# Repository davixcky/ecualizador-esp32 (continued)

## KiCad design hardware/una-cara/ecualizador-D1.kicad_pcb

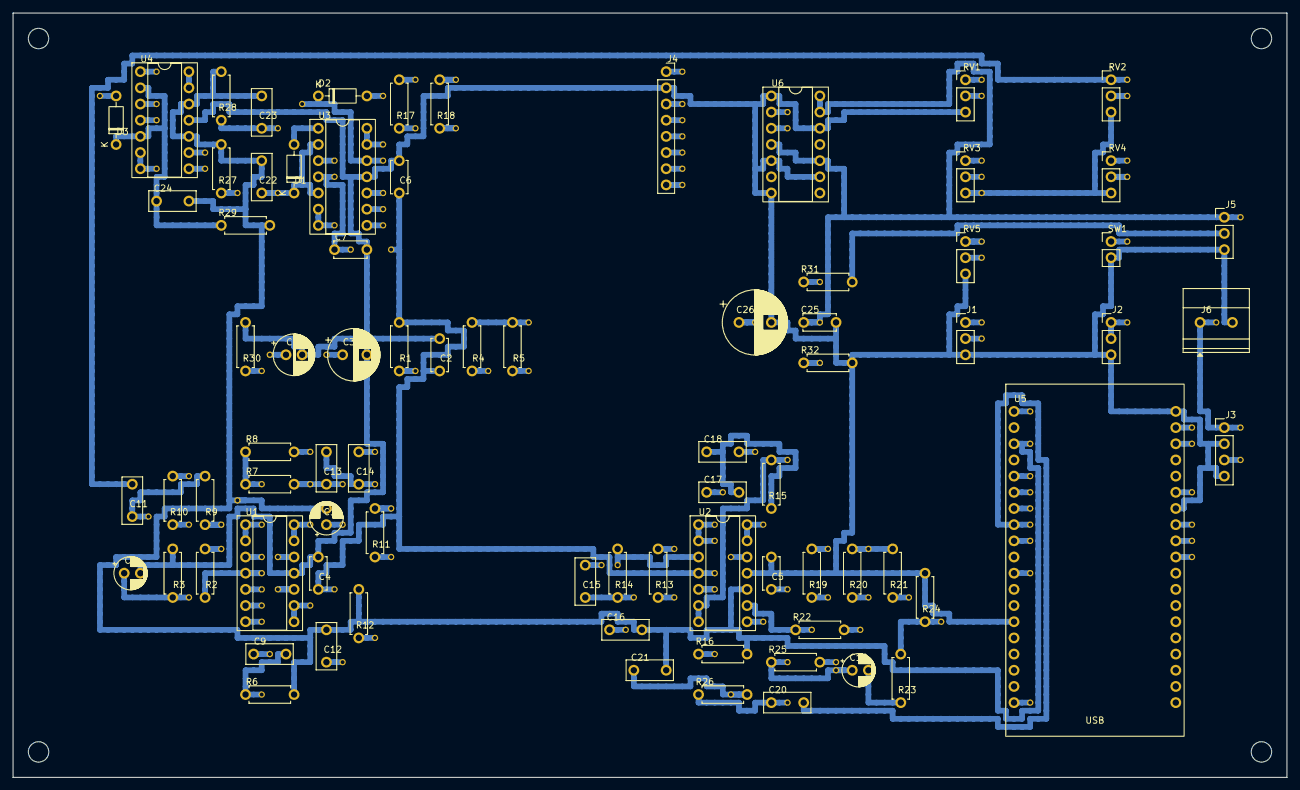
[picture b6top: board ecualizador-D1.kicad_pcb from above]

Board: 2 copper layers, 200.0 x 120.0 mm, 163 parts (0 on the bottom side), 59 nets.

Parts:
C1: 100u 10V; UnaCara_C1
C2: 100n; UnaCara_C2
C3: 470u 10V; UnaCara_C3
C4: 100n; UnaCara_C4
C5: 100n; UnaCara_C5
C6: 100n; UnaCara_C6
C7: 100n; UnaCara_C7
C8: 10u 16V; UnaCara_C8
C9: 1u film; UnaCara_C9
C10: 10u 16V; UnaCara_C10
C11: 100n film; UnaCara_C11
C12: 47n film; UnaCara_C12
C13: 10n film; UnaCara_C13
C14: 10n film; UnaCara_C14
C15: 10n film; UnaCara_C15
C16: 4n7 film; UnaCara_C16
C17: 10n film; UnaCara_C17
C18: 10n film; UnaCara_C18
C19: 10u 16V; UnaCara_C19
C20: 4n7 film; UnaCara_C20
C21: 2n2 film; UnaCara_C21
C22: 100n film; UnaCara_C22
C23: 100n film; UnaCara_C23
C24: 100n film; UnaCara_C24
C25: 100n; UnaCara_C25
C26: 1000u 10V; UnaCara_C26
D1: 1N4148; UnaCara_D1
D2: 1N4148; UnaCara_D2
D3: 1N4148; UnaCara_D3
H1, H2, H3, H4: MountingHole_3.2mm_M3
J1: Entrada de línea 3,5 mm; UnaCara_J1
J2: Salida de línea 3,5 mm; UnaCara_J2
J3: PAM8403; UnaCara_J3
J4: Waveshare 1.9 ST7789V2; UnaCara_J4
J5: NeoPixel 5V DIN GND; UnaCara_J5
J6: Entrada 5V 3A; UnaCara_J6
R1: 10; UnaCara_R1
R2: 10k 1%; UnaCara_R2
R3: 10k 1%; UnaCara_R3
R4: 10k; UnaCara_R4
R5: 10k; UnaCara_R5
R6: 100k; UnaCara_R6
R7: 22k 1%; UnaCara_R7
R8: 10k 1%; UnaCara_R8
R9: 10k 1%; UnaCara_R9
R10: 10k 1%; UnaCara_R10
R11: 27k 1%; UnaCara_R11
R12: 56k 1%; UnaCara_R12
R13: 10k 1%; UnaCara_R13
R14: 10k 1%; UnaCara_R14
R15: 2k7 1%; UnaCara_R15
R16: 5k6 1%; UnaCara_R16
R17: 47k 1%; UnaCara_R17
R18: 47k 1%; UnaCara_R18
R19: 47k 1%; UnaCara_R19
R20: 47k 1%; UnaCara_R20
R21: 47k 1%; UnaCara_R21
R22: 100k 1%; UnaCara_R22
R23: 100; UnaCara_R23
R24: 47k; UnaCara_R24
R25: 10k 1%; UnaCara_R25
R26: 10k 1%; UnaCara_R26
R27: 220k; UnaCara_R27
R28: 220k; UnaCara_R28
R29: 220k; UnaCara_R29
R30: 10k; UnaCara_R30
R31: 330; UnaCara_R31
R32: 10k; UnaCara_R32
RV1: 10k log; UnaCara_RV1
RV2: 10k lin; UnaCara_RV2
RV3: 10k lin; UnaCara_RV3
RV4: 10k lin; UnaCara_RV4
RV5: 10k log; UnaCara_RV5
SW1: Pulsador; UnaCara_SW1
U1: MCP6004; UnaCara_U1
U2: MCP6004; UnaCara_U2
U3: MCP6004; UnaCara_U3
U4: MCP6004; UnaCara_U4
U5: ESP32-DevKitC V4; UnaCara_U5
U6: 74AHCT125; UnaCara_U6
W1, W2: Cable aislado /VREF
W3, W4, W5, W6, W7: Cable aislado +3.3VA
W8, W9, W10, W11: Cable aislado +5V
W12, W13: Cable aislado /LINEA
W14, W15, W16: Cable aislado /PRE
W17: Cable aislado Net-(D1-K)
W18, W19: Cable aislado Net-(D2-K)
W20, W21: Cable aislado Net-(U2C--)
W22: Cable aislado /ADC_FFT
W23: Cable aislado /AGUDOS
W24, W25: Cable aislado /EQ_OUT
W26: Cable aislado /GRAVES
W27, W28: Cable aislado /MEDIOS
W29, W30: Cable aislado /MED_HP
W31, W32: Cable aislado Net-(U1A-+)
W33, W34: Cable aislado +3V3
W35: Cable aislado /ADC_A
W36: Cable aislado /ADC_G
W37: Cable aislado /ADC_M
W38, W39: Cable aislado /A_W
W40, W41: Cable aislado /G_W
W42, W43: Cable aislado /LED_DATA
W44, W45: Cable aislado /M_INV
W46, W47: Cable aislado /M_W
W48, W49: Cable aislado /TFT_BL
W50: Cable aislado Net-(C11-Pad1)
W51: Cable aislado Net-(C13-Pad2)
W52: Cable aislado Net-(C15-Pad1)
W53: Cable aislado Net-(C20-Pad1)
W54: Cable aislado Net-(R4-Pad2)
W55: Cable aislado Net-(U1B-+)
W56: Cable aislado Net-(U1B--)
W57, W58: Cable aislado Net-(U1C-+)
W59, W60: Cable aislado Net-(U1D-+)
W61: Cable aislado Net-(U2A-+)
W62, W63: Cable aislado Net-(U2B-+)
W64: Cable aislado Net-(U2D-+)
W65, W66: Cable aislado Net-(U4C--)
W67: Cable aislado /AMP_IN
W68: Cable aislado /BTN
W69: Cable aislado /IN_L
W70: Cable aislado /IN_R
W71: Cable aislado /LED_5V
W72: Cable aislado /TFT_CS
W73: Cable aislado /TFT_DC
W74: Cable aislado /TFT_MOSI
W75: Cable aislado /TFT_RST
W76: Cable aislado /TFT_SCK
W77: Cable aislado Net-(C10-Pad1)
W78: Cable aislado Net-(C9-Pad1)
W79: Cable aislado Net-(D2-A)
W80: Cable aislado Net-(D3-A)

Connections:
+3.3VA: C1.1, C2.1, C4.1, C5.1, C6.1, C7.1, R1.2, R2.1, U1.4, U2.4, U3.4, U4.4, W3.1, W3.2, W4.1, W4.2, W5.1, W5.2, W6.1, W6.2, W7.1, W7.2
+3V3: J4.1, R1.1, U5.1, W33.1, W33.2, W34.1, W34.2
+5V: C3.1, C25.1, C26.1, J3.1, J5.1, J6.1, U5.19, U6.4, U6.10, U6.13, U6.14, W8.1, W8.2, W9.1, W9.2, W10.1, W10.2, W11.1, W11.2
/ADC_A: U4.6, U4.7, U5.7, W35.1, W35.2
/ADC_FFT: C20.2, U2.13, U2.14, U5.8, W22.1, W22.2
/ADC_G: U3.6, U3.7, U5.5, W36.1, W36.2
/ADC_M: U3.13, U3.14, U5.6, W37.1, W37.2
/AGUDOS: R15.2, RV4.1, U2.6, U2.7, W23.1, W23.2
/AMP_IN: J3.3, RV5.2, W67.1, W67.2
/A_W: R21.1, RV4.2, U4.3, W38.1, W38.2, W39.1, W39.2
/BTN: SW1.1, U5.11, W68.1, W68.2
/EQ_OUT: C19.1, R22.2, R25.1, U2.8, W24.1, W24.2, W25.1, W25.2
/GRAVES: C11.2, RV2.1, U1.8, U1.9, W26.1, W26.2
/G_W: R19.1, RV2.2, U3.3, W40.1, W40.2, W41.1, W41.2
/IN_L: J1.T, R4.1, W69.1, W69.2
/IN_R: J1.R, R5.1, W70.1, W70.2
/LED_5V: R31.1, U6.3, W71.1, W71.2
/LED_DATA: R32.1, U5.9, U6.2, W42.1, W42.2, W43.1, W43.2
/LED_DIN: J5.2, R31.2
/LINEA: J2.R, J2.T, R23.2, R24.1, RV5.1, W12.1, W12.2, W13.1, W13.2
/MEDIOS: C15.2, RV3.1, U2.1, U2.2, W27.1, W27.2, W28.1, W28.2
/MED_HP: R11.2, R13.1, U1.13, U1.14, W29.1, W29.2, W30.1, W30.2
/M_INV: R18.2, R20.1, U4.8, W44.1, W44.2, W45.1, W45.2
/M_W: R17.1, RV3.2, U3.10, W46.1, W46.2, W47.1, W47.2
/PRE: C13.1, C17.1, R7.2, R9.1, U1.7, W14.1, W14.2, W15.1, W15.2, W16.1, W16.2
/TFT_BL: J4.8, R30.1, U5.27, W48.1, W48.2, W49.1, W49.2
/TFT_CS: J4.5, U5.29, W72.1, W72.2
/TFT_DC: J4.6, U5.25, W73.1, W73.2
/TFT_MOSI: J4.3, U5.21, W74.1, W74.2
/TFT_RST: J4.7, U5.22, W75.1, W75.2
/TFT_SCK: J4.4, U5.28, W76.1, W76.2
/VREF: C10.2, C12.2, C16.2, C21.2, C22.2, C23.2, C24.2, R6.2, R12.2, R16.2, R27.2, R28.2, R29.2, RV2.3, RV3.3, RV4.3, U1.1, U1.2, U2.10, U4.10, U4.12, U5.3, W1.1, W1.2, W2.1, W2.2
GND: C1.2, C2.2, C3.2, C4.2, C5.2, C6.2, C7.2, C8.2, C25.2, C26.2, J1.S, J2.S, J3.2, J3.4, J4.2, J5.3, J6.2, R3.2, R24.2, R30.2, R32.2, RV1.3, RV5.3, SW1.2, U1.11, U2.11, U3.11, U4.11, U5.14, U5.20, U5.26, U6.1, U6.5, U6.7, U6.9, U6.12
unnamed: C9.1, RV1.2, W78.1, W78.2
unnamed: C10.1, R8.2, W77.1, W77.2
unnamed: C11.1, R9.2, R10.1, W50.1, W50.2
unnamed: C13.2, C14.1, R11.1, W51.1, W51.2
unnamed: C15.1, R13.2, R14.1, W52.1, W52.2
unnamed: C17.2, C18.1, R15.1
unnamed: C19.2, R23.1
unnamed: C20.1, R25.2, R26.1, W53.1, W53.2
unnamed: D1.2, U3.1
unnamed: C22.1, D1.1, R27.1, U3.2, U3.5, W17.1, W17.2
unnamed: D2.2, U3.8, W79.1, W79.2
unnamed: C23.1, D2.1, R28.1, U3.9, U3.12, W18.1, W18.2, W19.1, W19.2
unnamed: D3.2, U4.1, W80.1, W80.2
unnamed: C24.1, D3.1, R29.1, U4.2, U4.5
unnamed: R4.2, R5.2, RV1.1, W54.1, W54.2
unnamed: C8.1, R2.2, R3.1, U1.3, W31.1, W31.2, W32.1, W32.2
unnamed: C9.2, R6.1, U1.5, W55.1, W55.2
unnamed: R7.1, R8.1, U1.6, W56.1, W56.2
unnamed: C12.1, R10.2, U1.10, W57.1, W57.2, W58.1, W58.2
unnamed: C14.2, R12.1, U1.12, W59.1, W59.2, W60.1, W60.2
unnamed: C16.1, R14.2, U2.3, W61.1, W61.2
unnamed: C18.2, R16.1, U2.5, W62.1, W62.2, W63.1, W63.2
unnamed: R19.2, R20.2, R21.2, R22.1, U2.9, W20.1, W20.2, W21.1, W21.2
unnamed: C21.1, R26.2, U2.12, W64.1, W64.2
unnamed: R17.2, R18.1, U4.9, W65.1, W65.2, W66.1, W66.2
unnamed: U4.13, U4.14

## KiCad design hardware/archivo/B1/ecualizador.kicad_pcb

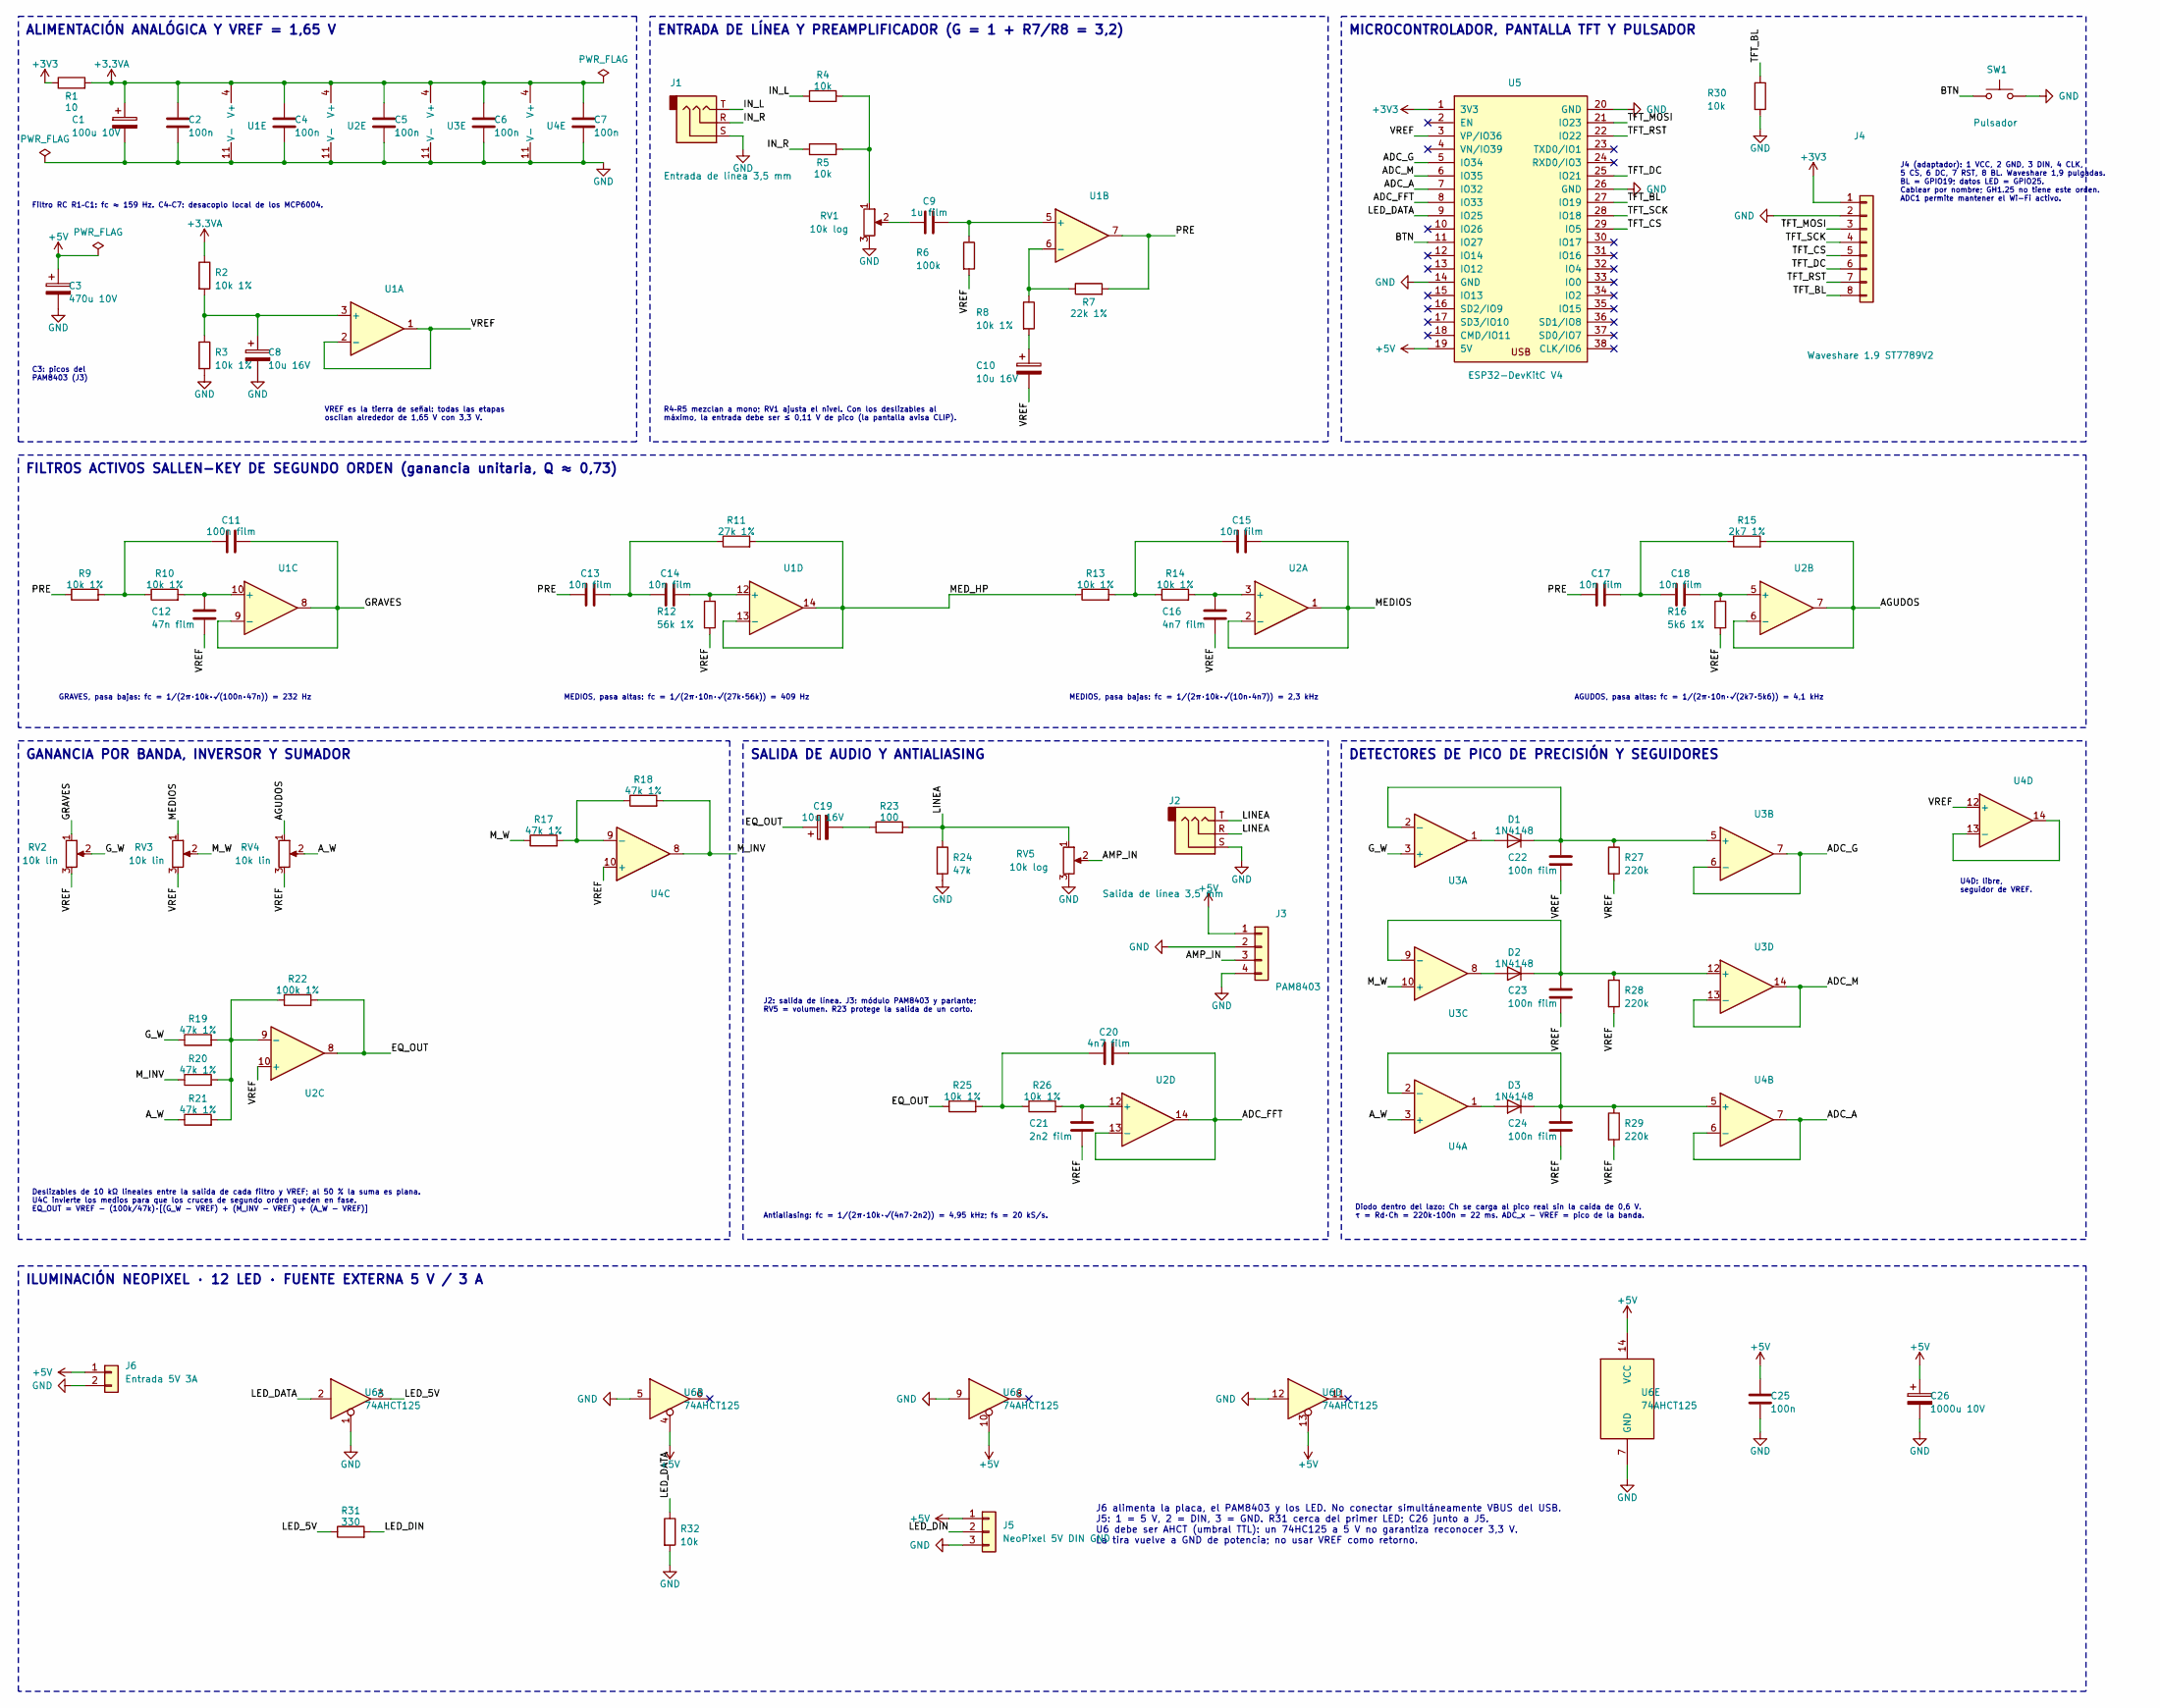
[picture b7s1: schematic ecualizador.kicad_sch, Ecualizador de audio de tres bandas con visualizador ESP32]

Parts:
C1: 100u 10V; UnaCara_C1
C2: 100n; UnaCara_C2
C3: 470u 10V; UnaCara_C3
C4: 100n; UnaCara_C4
C5: 100n; UnaCara_C5
C6: 100n; UnaCara_C6
C7: 100n; UnaCara_C7
C8: 10u 16V; UnaCara_C8
C9: 1u film; UnaCara_C9
C10: 10u 16V; UnaCara_C10
C11: 100n film; UnaCara_C11
C12: 47n film; UnaCara_C12
C13: 10n film; UnaCara_C13
C14: 10n film; UnaCara_C14
C15: 10n film; UnaCara_C15
C16: 4n7 film; UnaCara_C16
C17: 10n film; UnaCara_C17
C18: 10n film; UnaCara_C18
C19: 10u 16V; UnaCara_C19
C20: 4n7 film; UnaCara_C20
C21: 2n2 film; UnaCara_C21
C22: 100n film; UnaCara_C22
C23: 100n film; UnaCara_C23
C24: 100n film; UnaCara_C24
C25: 100n; UnaCara_C25
C26: 1000u 10V; UnaCara_C26
D1: 1N4148; UnaCara_D1
D2: 1N4148; UnaCara_D2
D3: 1N4148; UnaCara_D3
J1: Entrada de línea 3,5 mm; UnaCara_J1
J2: Salida de línea 3,5 mm; UnaCara_J2
J3: PAM8403; UnaCara_J3
J4: Waveshare 1.9 ST7789V2; UnaCara_J4
J5: NeoPixel 5V DIN GND; UnaCara_J5
J6: Entrada 5V 3A; UnaCara_J6
R1: 10; UnaCara_R1
R2: 10k 1%; UnaCara_R2
R3: 10k 1%; UnaCara_R3
R4: 10k; UnaCara_R4
R5: 10k; UnaCara_R5
R6: 100k; UnaCara_R6
R7: 22k 1%; UnaCara_R7
R8: 10k 1%; UnaCara_R8
R9: 10k 1%; UnaCara_R9
R10: 10k 1%; UnaCara_R10
R11: 27k 1%; UnaCara_R11
R12: 56k 1%; UnaCara_R12
R13: 10k 1%; UnaCara_R13
R14: 10k 1%; UnaCara_R14
R15: 2k7 1%; UnaCara_R15
R16: 5k6 1%; UnaCara_R16
R17: 47k 1%; UnaCara_R17
R18: 47k 1%; UnaCara_R18
R19: 47k 1%; UnaCara_R19
R20: 47k 1%; UnaCara_R20
R21: 47k 1%; UnaCara_R21
R22: 100k 1%; UnaCara_R22
R23: 100; UnaCara_R23
R24: 47k; UnaCara_R24
R25: 10k 1%; UnaCara_R25
R26: 10k 1%; UnaCara_R26
R27: 220k; UnaCara_R27
R28: 220k; UnaCara_R28
R29: 220k; UnaCara_R29
R30: 10k; UnaCara_R30
R31: 330; UnaCara_R31
R32: 10k; UnaCara_R32
RV1: 10k log; UnaCara_RV1
RV2: 10k lin; UnaCara_RV2
RV3: 10k lin; UnaCara_RV3
RV4: 10k lin; UnaCara_RV4
RV5: 10k log; UnaCara_RV5
SW1: Pulsador; UnaCara_SW1
U1: MCP6004; UnaCara_U1
U2: MCP6004; UnaCara_U2
U3: MCP6004; UnaCara_U3
U4: MCP6004; UnaCara_U4
U5: ESP32-DevKitC V4; UnaCara_U5
U6: 74AHCT125; UnaCara_U6

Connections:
+3.3VA: C1.1, C2.1, C4.1, C5.1, C6.1, C7.1, R1.2, R2.1, U1.4 (V+), U2.4 (V+), U3.4 (V+), U4.4 (V+)
+3V3: J4.1, R1.1, U5.1 (3V3)
+5V: C3.1, C25.1, C26.1, J3.1, J5.1, J6.1, U5.19 (5V), U6.4, U6.10, U6.13, U6.14 (VCC)
/ADC_A: U4.6 (-), U4.7, U5.7 (IO32)
/ADC_FFT: C20.2, U2.13 (-), U2.14, U5.8 (IO33)
/ADC_G: U3.6 (-), U3.7, U5.5 (IO34)
/ADC_M: U3.13 (-), U3.14, U5.6 (IO35)
/AGUDOS: R15.2, RV4.1, U2.6 (-), U2.7
/AMP_IN: J3.3, RV5.2
/A_W: R21.1, RV4.2, U4.3 (+)
/BTN: SW1.1, U5.11 (IO27)
/EQ_OUT: C19.1, R22.2, R25.1, U2.8
/GRAVES: C11.2, RV2.1, U1.8, U1.9 (-)
/G_W: R19.1, RV2.2, U3.3 (+)
/IN_L: J1.T, R4.1
/IN_R: J1.R, R5.1
/LED_5V: R31.1, U6.3
/LED_DATA: R32.1, U5.9 (IO25), U6.2
/LED_DIN: J5.2, R31.2
/LINEA: J2.R, J2.T, R23.2, R24.1, RV5.1
/MEDIOS: C15.2, RV3.1, U2.1, U2.2 (-)
/MED_HP: R11.2, R13.1, U1.13 (-), U1.14
/M_INV: R18.2, R20.1, U4.8
/M_W: R17.1, RV3.2, U3.10 (+)
/PRE: C13.1, C17.1, R7.2, R9.1, U1.7
/TFT_BL: J4.8, R30.1, U5.27 (IO19)
/TFT_CS: J4.5, U5.29 (IO5)
/TFT_DC: J4.6, U5.25 (IO21)
/TFT_MOSI: J4.3, U5.21 (IO23)
/TFT_RST: J4.7, U5.22 (IO22)
/TFT_SCK: J4.4, U5.28 (IO18)
/VREF: C10.2, C12.2, C16.2, C21.2, C22.2, C23.2, C24.2, R6.2, R12.2, R16.2, R27.2, R28.2, R29.2, RV2.3, RV3.3, RV4.3, U1.1, U1.2 (-), U2.10 (+), U4.10 (+), U4.12 (+), U5.3 (VP/IO36)
GND: C1.2, C2.2, C3.2, C4.2, C5.2, C6.2, C7.2, C8.2, C25.2, C26.2, J1.S, J2.S, J3.2, J3.4, J4.2, J5.3, J6.2, R3.2, R24.2, R30.2, R32.2, RV1.3, RV5.3, SW1.2, U1.11 (V-), U2.11 (V-), U3.11 (V-), U4.11 (V-), U5.14 (GND), U5.20 (GND), U5.26 (GND), U6.1, U6.5, U6.7 (GND), U6.9, U6.12
unnamed: C9.1, RV1.2
unnamed: C10.1, R8.2
unnamed: C11.1, R9.2, R10.1
unnamed: C13.2, C14.1, R11.1
unnamed: C15.1, R13.2, R14.1
unnamed: C17.2, C18.1, R15.1
unnamed: C19.2, R23.1
unnamed: C20.1, R25.2, R26.1
unnamed: D1.2 (A), U3.1
unnamed: C22.1, D1.1 (K), R27.1, U3.2 (-), U3.5 (+)
unnamed: D2.2 (A), U3.8
unnamed: C23.1, D2.1 (K), R28.1, U3.9 (-), U3.12 (+)
unnamed: D3.2 (A), U4.1
unnamed: C24.1, D3.1 (K), R29.1, U4.2 (-), U4.5 (+)
unnamed: R4.2, R5.2, RV1.1
unnamed: C8.1, R2.2, R3.1, U1.3 (+)
unnamed: C9.2, R6.1, U1.5 (+)
unnamed: R7.1, R8.1, U1.6 (-)
unnamed: C12.1, R10.2, U1.10 (+)
unnamed: C14.2, R12.1, U1.12 (+)
unnamed: C16.1, R14.2, U2.3 (+)
unnamed: C18.2, R16.1, U2.5 (+)
unnamed: R19.2, R20.2, R21.2, R22.1, U2.9 (-)
unnamed: C21.1, R26.2, U2.12 (+)
unnamed: R17.2, R18.1, U4.9 (-)
unnamed: U4.13 (-), U4.14

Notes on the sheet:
ALIMENTACIÓN ANALÓGICA Y VREF = 1,65 V
Filtro RC R1–C1: fc ≈ 159 Hz. C4–C7: desacoplo local de los MCP6004.
C3: picos del PAM8403 (J3)
VREF es la tierra de señal: todas las etapas oscilan alrededor de 1,65 V con 3,3 V.
ENTRADA DE LÍNEA Y PREAMPLIFICADOR (G = 1 + R7/R8 = 3,2)
R4–R5 mezclan a mono; RV1 ajusta el nivel. Con los deslizables al máximo, la entrada debe ser ≤ 0,11 V de pico (la pantalla avisa CLIP).
MICROCONTROLADOR, PANTALLA TFT Y PULSADOR
J4 (adaptador): 1 VCC, 2 GND, 3 DIN, 4 CLK, 5 CS, 6 DC, 7 RST, 8 BL. Waveshare 1,9 pulgadas. BL = GPIO19; datos LED = GPIO25. Cablear por nombre; GH1.25 no tiene este orden. ADC1 permite mantener el Wi-Fi activo.
FILTROS ACTIVOS SALLEN-KEY DE SEGUNDO ORDEN (ganancia unitaria, Q ≈ 0,73)
GRAVES, pasa bajas: fc = 1/(2π·10k·√(100n·47n)) = 232 Hz
MEDIOS, pasa altas: fc = 1/(2π·10n·√(27k·56k)) = 409 Hz
MEDIOS, pasa bajas: fc = 1/(2π·10k·√(10n·4n7)) = 2,3 kHz
AGUDOS, pasa altas: fc = 1/(2π·10n·√(2k7·5k6)) = 4,1 kHz
GANANCIA POR BANDA, INVERSOR Y SUMADOR
Deslizables de 10 kΩ lineales entre la salida de cada filtro y VREF; al 50 % la suma es plana. U4C invierte los medios para que los cruces de segundo orden queden en fase. EQ_OUT = VREF − (100k/47k)·[(G_W − VREF) + (M_INV − VREF) + (A_W − VREF)]
SALIDA DE AUDIO Y ANTIALIASING
J2: salida de línea. J3: módulo PAM8403 y parlante; RV5 = volumen. R23 protege la salida de un corto.
Antialiasing: fc = 1/(2π·10k·√(4n7·2n2)) = 4,95 kHz; fs = 20 kS/s.
DETECTORES DE PICO DE PRECISIÓN Y SEGUIDORES
U4D: libre, seguidor de VREF.
Diodo dentro del lazo: Ch se carga al pico real sin la caída de 0,6 V. τ = Rd·Ch = 220k·100n = 22 ms. ADC_x − VREF = pico de la banda.
ILUMINACIÓN NEOPIXEL · 12 LED · FUENTE EXTERNA 5 V / 3 A
J6 alimenta la placa, el PAM8403 y los LED. No conectar simultáneamente VBUS del USB. J5: 1 = 5 V, 2 = DIN, 3 = GND. R31 cerca del primer LED; C26 junto a J5. U6 debe ser AHCT (umbral TTL): un 74HC125 a 5 V no garantiza reconocer 3,3 V. La tira vuelve a GND de potencia; no usar VREF como retorno.

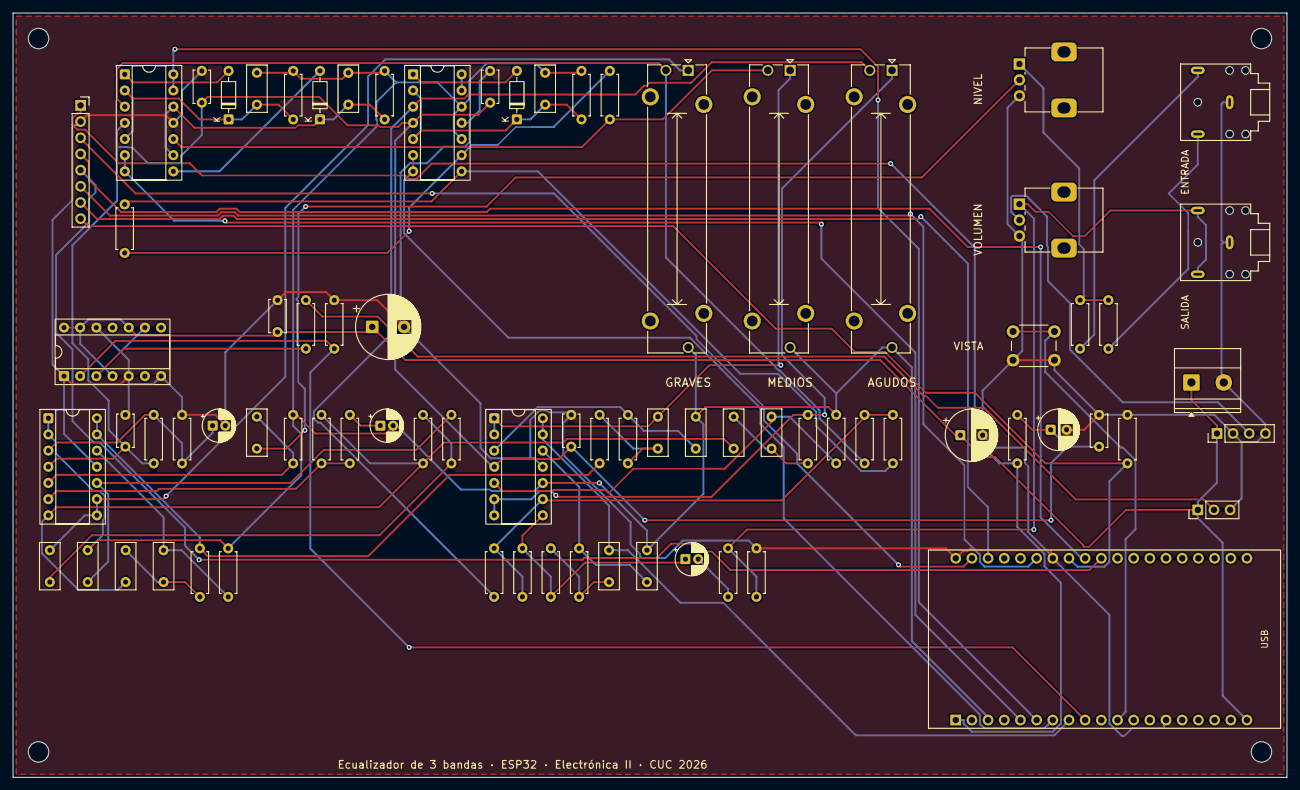
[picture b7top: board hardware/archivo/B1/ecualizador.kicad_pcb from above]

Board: 2 copper layers, 200.0 x 120.0 mm, 83 parts (0 on the bottom side), 59 nets.

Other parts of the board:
H1, H2, H3, H4: MountingHole_3.2mm_M3

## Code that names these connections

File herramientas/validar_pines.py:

#!/usr/bin/env python3
"""Cruza los GPIO del firmware con las señales del esquema, sin compilar ni alimentar la placa."""
from pathlib import Path
import re
import circuito
root=Path(__file__).resolve().parents[1]
config=(root/'firmware/include/config.h').read_text()
defines={k:int(v) for k,v in re.findall(r'^#define\s+(\w+)\s+(-?\d+)',config,re.M)}
mapping={'PIN_VREF':'VREF','PIN_GRAVES':'ADC_G','PIN_MEDIOS':'ADC_M','PIN_AGUDOS':'ADC_A','PIN_FFT':'ADC_FFT','PIN_BOTON':'BTN','PIN_NEOPIXEL':'LED_DATA',**{x:x for x in ['TFT_CS','TFT_DC','TFT_RST','TFT_MOSI','TFT_SCK','TFT_BL']}}
pins=[]
for define,net in mapping.items():
    gpio=defines[define]
    label='VP/IO36' if gpio==36 else f'IO{gpio}'
    assert circuito.ESP_REDES[label]==net,(define,net)
    pins.append(gpio)
assert len(pins)==len(set(pins)), 'GPIO compartido'
assert defines['TFT_MISO']==-1
assert circuito.pieza('U6')['pines']=={'1':'GND','2':'LED_DATA','3':'LED_5V','4':'+5V','5':'GND','6':None,'7':'GND','8':None,'9':'GND','10':'+5V','11':None,'12':'GND','13':'+5V','14':'+5V'}
print(f'{len(pins)} GPIO coinciden; ninguno compartido; MISO desactivado; pinout AHCT125 comprobado.')

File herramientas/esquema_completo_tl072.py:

from pathlib import Path
import matplotlib; matplotlib.use('Agg')
import matplotlib.pyplot as plt
from matplotlib.patches import Polygon,Rectangle,Circle
import csv,json
root=Path(__file__).resolve().parents[1];out=root/'docs/prototipo-tl072'
fig,ax=plt.subplots(figsize=(23.4,16.5)); ax.set(xlim=(0,2600),ylim=(1760,0));ax.axis('off');fig.subplots_adjust(0,0,1,1)
wire='#166447';ink='#122b38';red='#a3161a'; drawn={}
def line(*pts,color=wire,lw=1.15):ax.plot(*zip(*pts),color=color,lw=lw)
def text(x,y,s,size=9,color=ink,ha='center'):ax.text(x,y,s,fontsize=size,color=color,ha=ha,va='center',fontfamily='DejaVu Sans')
def dot(x,y):ax.add_patch(Circle((x,y),3.2,color=wire))
def ground(x,y):
 line((x,y),(x,y+15));line((x-13,y+15),(x+13,y+15));line((x-9,y+21),(x+9,y+21));line((x-4,y+27),(x+4,y+27))
def part(ref,val,x1,y1,x2,y2,kind='R',nets=None):
 if nets:drawn[ref]=(val,*nets)
 vertical=x1==x2;cx=(x1+x2)/2;cy=(y1+y2)/2
 if vertical:
  line((x1,y1),(cx,cy-22));line((cx,cy+22),(x2,y2))
  if kind=='R':ax.add_patch(Rectangle((cx-9,cy-22),18,44,fill=False,edgecolor=ink,lw=1.2))
  else:line((cx,cy-22),(cx,cy-5));line((cx,cy+5),(cx,cy+22));line((cx-17,cy-5),(cx+17,cy-5),color=ink);line((cx-17,cy+5),(cx+17,cy+5),color=ink)
  text(cx-20 if ref.startswith('RV') else cx+22,cy,ref+'\n'+val,8,ha='right' if ref.startswith('RV') else 'left')
 else:
  line((x1,y1),(cx-22,cy));line((cx+22,cy),(x2,y2))
  if kind=='R':ax.add_patch(Rectangle((cx-22,cy-9),44,18,fill=False,edgecolor=ink,lw=1.2))
  else:line((cx-22,cy),(cx-5,cy));line((cx+5,cy),(cx+22,cy));line((cx-5,cy-17),(cx-5,cy+17),color=ink);line((cx+5,cy-17),(cx+5,cy+17),color=ink)
  text(cx,cy-31,ref+'  '+val,8)
def op(name,x,y,pins,inv=False):
 ax.add_patch(Polygon([(x,y-44),(x,y+44),(x+85,y)],fill=False,edgecolor=ink,lw=1.3))
 text(x+15,y-20,'−' if inv else '+',10);text(x+15,y+20,'+' if inv else '−',10)
 text(x+36,y,name,9);text(x+40,y+62,'TL072CP',7)
 text(x-9,y-32,str(pins[1] if inv else pins[0]),7);text(x-9,y+35,str(pins[0] if inv else pins[1]),7);text(x+94,y-13,str(pins[2]),7)
 return (x,y-20),(x,y+20),(x+85,y)
def follower(name,x,y,pins):
 a,b,o=op(name,x,y,pins);line(b,(x-20,y+20),(x-20,y+90),(x+120,y+90),(x+120,y),o);dot(x+120,y)
def filt(name,x,y,refs,values,source,target,internal,hp=False,pins=(3,2,1)):
 # Input y; op center y+20, output y+20.
 n1=x+130;n2=x+260;ox=x+330;end=x+470
 kind='C' if hp else 'R';other='R' if hp else 'C'
 part(refs[0],values[0],x,y,n1,y,kind,(source,internal[0]));part(refs[1],values[1],n1,y,n2,y,kind,(internal[0],internal[1]));line((n2,y),(ox,y));follower(name,ox,y+20,pins)
 line((n1,y),(n1,y-100));part(refs[2],values[2],n1,y-100,end,y-100,other,(internal[0],target));line((end,y-100),(end,y+20));dot(n1,y);dot(n2,y);dot(end,y+20)
 part(refs[3],values[3],n2,y,n2,y+120,other,(internal[1],'0'));ground(n2,y+120)
 line((ox+85,y+20),(end,y+20));text(end,y-12,target,8)
 return end,y+20
text(35,35,'ECUALIZADOR · PROTOTIPO TL072CP',20,red,ha='left');text(35,72,'Cadena analógica completa · 4 integrados DIP-8 · alimentación ±12 V · valores y referencias de la guía TL072',10,ha='left')
line((35,100),(2560,100),color=red)
text(55,170,'ENTRADA Y PREAMPLIFICADOR',11,red,ha='left')
# Preamp at x200 y620; source incoming from left
part('C1','1u',45,600,155,600,'C',('ENTRADA','IN'));text(48,567,'J1 · señal',8);part('R1','100k',155,600,155,745,'R',('IN','0'));ground(155,745);dot(155,600)
line((155,600),(220,600));op('U1A',220,620,(3,2,1));line((305,620),(385,620));text(365,590,'PRE',9)
line((220,640),(205,640),(205,830));part('R3','10k',205,830,205,930,'R',('FB','0'));ground(205,930)
part('R2','22k',205,830,385,830,'R',('PRE','FB'));line((385,830),(385,620));dot(205,830);dot(385,620)
text(65,1030,'J1 masa → 0 V\nGenerador: 100 mVpp\nSenoide, offset 0 V\nO audio mono de línea',9,ha='left')
# common PRE bus branches no crossings except the named output junction
line((385,620),(440,620),(440,270));line((440,620),(440,950));dot(440,620)
for yy in [270,620,950]:line((440,yy),(530,yy));dot(440,yy)
text(530,140,'GRAVES · PASA BAJAS · 232 Hz',11,red,ha='left')
g=filt('U1B',530,270,['R4','R5','C2','C3'],['10k','10k','100n','47n'],'PRE','GRAVES',['L1','L2'],pins=(5,6,7))
text(530,450,'MEDIOS · PASA ALTAS 409 Hz + PASA BAJAS 2,32 kHz',11,red,ha='left')
mh=filt('U2A',530,620,['C4','C5','R6','R7'],['10n','10n','27k','56k'],'PRE','MED_HP',['H1','H2'],hp=True)
line(mh,(1060,640),(1060,620),(1120,620))
m=filt('U2B',1120,620,['R8','R9','C6','C7'],['10k','10k','10n','4.7n'],'MED_HP','MEDIOS',['M1','M2'],pins=(5,6,7))
text(530,780,'AGUDOS · PASA ALTAS · 4,09 kHz',11,red,ha='left')
a=filt('U3A',530,950,['C8','C9','R10','R11'],['10n','10n','2.7k','5.6k'],'PRE','AGUDOS',['A1','A2'],hp=True)
# pots each output routed to far right, rightwards wiper
for i,(pt,yy,node) in enumerate([(g,290,'GW'),(m,640,'MW'),(a,970,'AW')],1):
 x=1685;line(pt,(x,yy));dot(x,yy);part('RV'+str(i),'10k LIN',x,yy,x,yy+140);ground(x,yy+140)
 ax.annotate('',xy=(x+9,yy+70),xytext=(x+65,yy+70),arrowprops={'arrowstyle':'->','color':wire,'lw':1.2});text(x+72,yy+47,node,8);text(x-16,yy+12,'1',7);text(x+30,yy+64,'2',7);text(x-16,yy+131,'3',7)
# middle inverter
part('R12','47k',1750,710,1900,710,'R',('MW','INV'));op('U3B',1920,730,(5,6,7),inv=True);line((1900,710),(1920,710));line((1920,750),(1900,750),(1900,820));ground(1900,820)
line((1900,710),(1900,620));part('R13','47k',1900,620,2050,620,'R',('INV','MI'));line((2050,620),(2050,730),(2005,730));dot(1900,710);dot(2050,730);text(2050,760,'MI',8)
# sum input three routes to node at x2240 y520
line((1750,360),(2060,360));part('R14','47k',2060,360,2240,360,'R',('GW','SUM'));line((2240,360),(2240,520),(2270,520));dot(2240,520)
line((2050,730),(2080,730),(2080,520));part('R15','47k',2080,520,2240,520,'R',('MI','SUM'))
line((1750,1040),(2150,1040),(2150,890));part('R16','47k',2150,890,2240,890,'R',('AW','SUM'));line((2240,890),(2240,520))
op('U4A',2270,540,(3,2,1),inv=True);line((2270,560),(2260,560),(2260,670));ground(2260,670)
line((2240,360),(2240,240));dot(2240,360);part('R17','100k',2240,240,2440,240,'R',('SUM','EQ'));line((2440,240),(2440,540),(2355,540));dot(2440,540);text(2440,574,'EQ',9)
line((2440,540),(2505,540),(2505,1000),(2260,1000))
part('C10','1u',2260,1000,2260,1130,'C',('EQ','AC'));part('R18','100',2260,1130,2420,1130,'R',('AC','SALIDA'));line((2420,1130),(2530,1130));text(2530,1095,'J2 SALIDA',9);dot(2420,1130);part('R19','47k',2420,1130,2420,1240,'R',('SALIDA','0'));ground(2420,1240)
text(1850,170,'CONTROLES, INVERSOR Y SUMADOR',11,red,ha='left');text(1850,1195,'Salida de línea: osciloscopio 1 MΩ\no entrada de parlante activo.\nMasa de J2 → 0 V.',9,ha='left')
# bottom power zone
line((35,1310),(2560,1310),color=red);text(35,1345,'ALIMENTACIÓN Y DESACOPLE · conectar en los cuatro TL072',11,red,ha='left')
for i,x in enumerate([450,710,970,1230],1):
 text(x,1380,f'U{i} · pin 8: +12 V / pin 4: −12 V',8)
 part('C'+str(9+i*2),'100n',x,1410,x,1500,'C');part('C'+str(10+i*2),'100n',x,1500,x,1590,'C');dot(x,1500);line((x,1500),(x-35,1500));ground(x-35,1500);text(x,1398,'+12 V',7);text(x,1612,'−12 V',7)
# rails named labels to each supply on schematic
text(45,1410,'J3 · alimentación\n1: +12 V → pin 8, U1–U4\n2: 0 V → todas las tierras\n3: −12 V → pin 4, U1–U4',9,ha='left')
text(45,1540,'Desacoples junto a cada IC.\nC11–C18: cerámicos.\nC19–C20: 47 µF / ≥25 V.',9,ha='left')
for x,ref,top,bottom in [(1510,'C19','+12 V','0 V'),(1770,'C20','0 V','−12 V')]:
 text(x,1410,top,8);part(ref,'47u',x,1435,x,1550,'C');text(x-29,1470,'+',12);text(x,1580,bottom,8)
text(1640,1630,'Respetar la polaridad indicada.',8)
op('U4B',2100,1470,(5,6,7));line((2100,1450),(2070,1450));ground(2070,1450);line((2100,1490),(2085,1490),(2085,1570),(2220,1570),(2220,1470),(2185,1470));text(2260,1530,'Canal libre:\n5 a 0 V; unir 6 y 7.',9,ha='left')
text(35,1690,'Notas: R en Ω; k = kΩ; u = µF; n = nF. C1–C10 no polarizados. Punto sólido = unión; cruce sin punto = sin conexión.',9,ha='left')
text(35,1720,'0 V es el punto medio de la fuente. Masas de instrumentos a 0 V. No conectar estas señales directamente al ESP32 ni a un parlante pasivo.',9,red,ha='left')
# compare all signal component refs/value/net pairs against established prototype CSV
expected={r['pieza']:(r['valor'],r['terminal_1'],r['terminal_2']) for r in csv.DictReader((out/'conexiones.csv').open())}
assert set(drawn)==set(expected)
for ref,(val,a,b) in drawn.items():
 ev,ea,eb=expected[ref];assert val==ev and {a,b}=={ea,eb},(ref,drawn[ref],expected[ref])
fig.savefig(out/'esquema-completo-grafico.pdf');fig.savefig(out/'esquema-completo.svg');fig.savefig(out/'esquema-completo.png',dpi=120)
(out/'validacion-esquema-completo.json').write_text(json.dumps({'pasivos_senal_coinciden_con_guia':len(drawn),'TL072':4,'desacoples':8,'reserva_riel':2,'validacion':'referencias, valores y redes de los 29 pasivos contra conexiones.csv; revisión visual de cableado','montaje_fisico_verificado':False},indent=2))
